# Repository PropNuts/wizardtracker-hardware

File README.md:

# STOP!

__This project has moved to GitLab:__ https://gitlab.com/PropNuts/wizardtracker-hardware

__There will be no further updates here.__

# wizardtracker-hardware

This project contains the hardware and firmware for the PropNuts WizardTracker,
an RSSI-based lap timer for drone racing.

## Hardware

The KiCad files can be found under `hardware/`.

The current revision (v2) allows for a total of either eight receivers, or six
receivers with voltage and temperature monitoring. A voltage regulator and XT60
are mounted onboard to provide power.

<p>
  
</p>

### Parts List

You can put together a full system for around ~£65.

- [RX5808s (6x or 8x)](https://www.banggood.com/FPV-5_8G-Wireless-Audio-Video-Receiving-Module-RX5808-p-84775.html?p=U103211727939201506N)
- [Arduino Nano](https://www.banggood.com/ATmega328P-Nano-V3-Controller-Board-Compatible-Arduino-p-940937.html?p=U103211727939201506N)
- [BEC (5V)](https://www.banggood.com/Diatone-Mini-2A-BEC-V2_0-Version-3_3V-5V-12V-For-RC-Multirotors-p-1032859.html?p=U103211727939201506N)
- [XT60](https://www.banggood.com/10X-XT60-Male-Female-Bullet-Connectors-Plugs-For-RC-Battery-p-958017.html?p=U103211727939201506N)
- [LM35](https://www.banggood.com/3Pcs-LM35DZ-TO-92-LM35-Precision-Centigrade-Temperature-Sensor-p-1091397.html?p=U103211727939201506N)
- [Resistors (1x 330, 1x 10k, 1x 100k)](https://www.banggood.com/Wholesale-Metal-Film-Resistor-Assorted-Kit-30-Kinds-Value-Total-600pcs-20pcs-Each-p-53320.html?p=U103211727939201506N)
- [LEDs](https://www.banggood.com/100pcs-3mm-LED-Light-emitting-Diode-5-Colors-Electronic-Component-Pack-p-1106574.html?p=U103211727939201506N)
- [Schottky Diode (1x 1N5817)](https://www.banggood.com/100-Pcs-030892-Diodes-Package-Rectifier-Schottky-8-Type-In-Component-Box-p-1164787.html?p=U103211727939201506N)
- [Pin Headers](https://www.banggood.com/10-Pcs-40-Pin-2_54mm-Single-Row-Male-Pin-Header-Strip-For-Arduino-p-918427.html?p=U103211727939201506N)

_These are affiliate links._

## Firmware

1. Grab the latest version of the Arduino IDE.
2. Clone the repository and open `firmware/firmware.ino`.
3. Edit `Config.h` to your needs.
4. Compile and flash the code.
5. Pray the magic smoke stays in.

### Protocol

On boot, the firmware opens serial at `250000bps`. After a short delay, it will
begin sending RSSI values for each module, seperated by a space, ending in a new
line. Each line is prefixd with `r `.

In calibrated output mode, values range between `0` to `255`. In raw output
mode (default), values range between `0` to  `1023`.

    < r 110 220 150 243 135 254
    < r 140 231 143 192 148 244
    ... etc

If enabled, voltage and temperature values will be sent periodically. Voltage
is prefixed with `v ` and temperature is prefixed with `t `.

    < v 16.08
    < t 56.33
    ... etc

#### Commands

The command parser is extremely niave, with little to no error checking. Expect
strange results with malformed commands. All command should end in a new line
character.

Frequencies can be set by sending `f <index> <frequency>`. These frequencies
will be saved and reloaded on startup.

    > f 0 5745
    < ok
    > f 1 5975
    < ok
    ... etc

Modules can be calibrated using `n` (minimum) and `m` (maximum). These
calibration values will be saved and reloaded on startup. The device must be
rebooted for calibration to take effect.

    [all modules set to same frequency]
    [transmitter powered down]
    > n
    < ok
    [transmitter powered up]
    > m
    < ok

Output can be toggled between raw output using `r`, and calibration output
using `s`. The default mode is raw output. This setting is saved and will be
reloaded on startup.

    > r
    < ok
    < r 395 345 299 405 514 445
    < ... etc
    > s
    < ok
    < r 0 5 8 1 10 13
    < ... etc

Information about the device can be requested using `?`. The device will respond
in the format `? <module count> <frequency 1>...<frequency n> <raw mode>`.

    > ?
    < ? 6 5695 5695 5695 5695 5695 5695 1
    [6 receivers all on 5695MHz, with raw mode enabled]
    < ok

## Acknowledgements

The source code for this project is based on [my rx5808-pro-diversity rewrite](https://github.com/Knifa/rx5808-pro-diversity/tree/tidy-up).

## License

This project is licensed under the terms of the MIT license.

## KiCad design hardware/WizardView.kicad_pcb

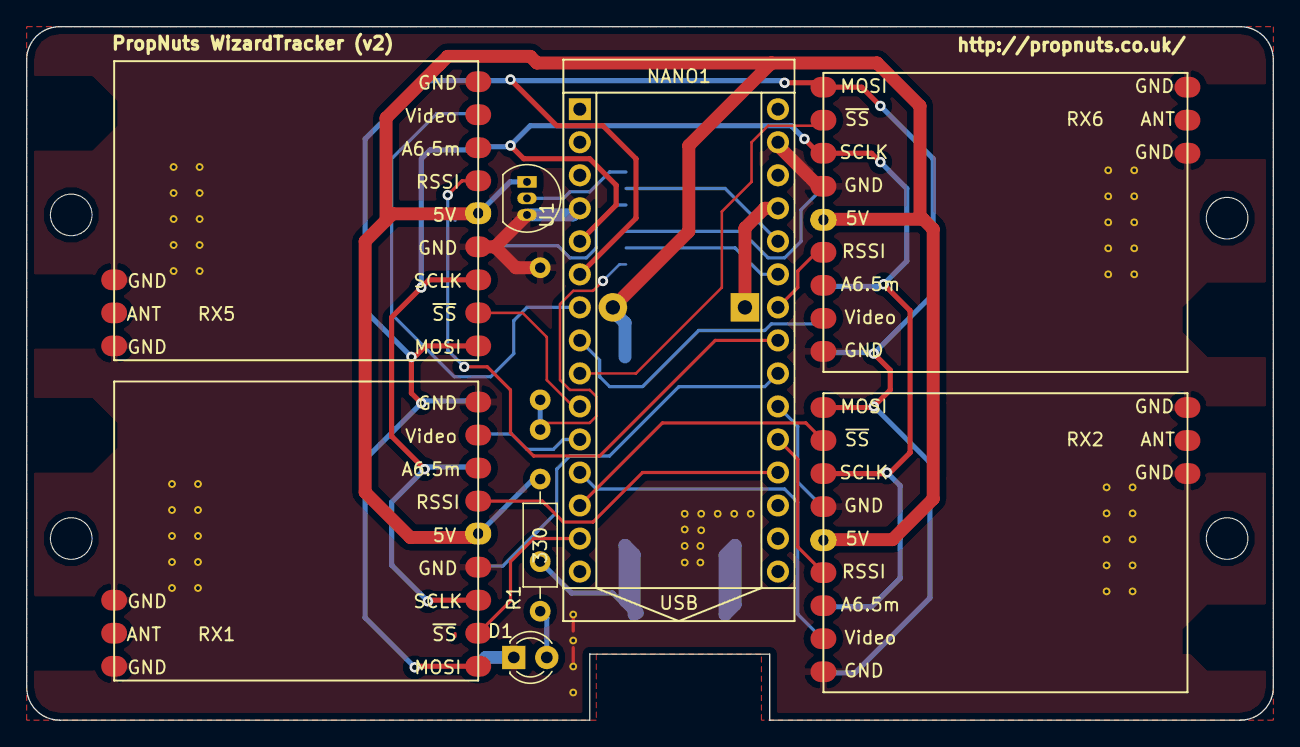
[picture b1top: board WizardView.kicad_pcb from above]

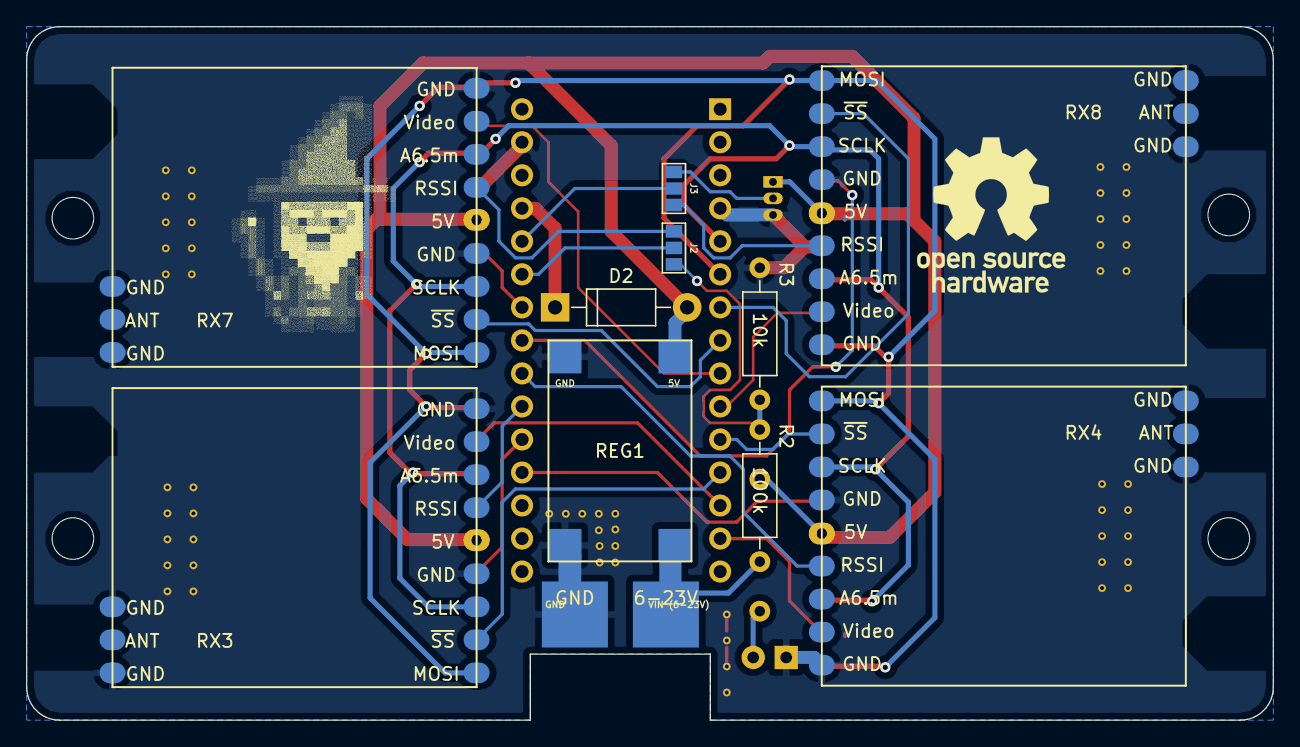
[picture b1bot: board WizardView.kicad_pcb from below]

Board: 2 copper layers, 95.9 x 53.3 mm, 19 parts (11 on the bottom side), 27 nets.

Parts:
D1: LED; LED_D3.0mm
D2: D_Schottky; D_DO-41_SOD81_P10.16mm_Horizontal
J1: CONN_01X02; XT60_5V
J2, J3: GS3
NANO1: ArduinoNano
R1: 330; R_Axial_DIN0207_L6.3mm_D2.5mm_P10.16mm_Horizontal
R2: 100k; R_Axial_DIN0207_L6.3mm_D2.5mm_P10.16mm_Horizontal
R3: 10k; R_Axial_DIN0207_L6.3mm_D2.5mm_P10.16mm_Horizontal
REG1: 5VRegulator; 5VBEC
RX1, RX2, RX3, RX4, RX5, RX6, RX7, RX8: RX5808
U1: LM35-LP; TO-92_Inline_Narrow_Oval

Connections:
+5V: D2.2, R1.1, REG1.3, RX1.5, RX2.5, RX3.5, RX4.5, RX5.5, RX6.5, RX7.5, RX8.5, U1.1
+BATT: J1.2, R2.1, REG1.1
/BATTDIV: J2.3, R2.2, R3.1
/MOSI: NANO1.6, RX1.9, RX2.9, RX3.9, RX4.9, RX5.9, RX6.9, RX7.9, RX8.9
/RSSI1: NANO1.27, RX1.4
/RSSI2: NANO1.26, RX2.4
/RSSI3: NANO1.25, RX3.4
/RSSI4: NANO1.24, RX4.4
/RSSI5: NANO1.23, RX5.4
/RSSI6: NANO1.22, RX6.4
/RSSI7: J2.1, RX7.4
/RSSI8: J3.1, RX8.4
/SCLK: NANO1.5, RX1.7, RX2.7, RX3.7, RX4.7, RX5.7, RX6.7, RX7.7, RX8.7
/TEMP: J3.3, U1.2
/~SS1: NANO1.14, RX1.8
/~SS2: NANO1.13, RX2.8
/~SS3: NANO1.12, RX3.8
/~SS4: NANO1.11, RX4.8
/~SS5: NANO1.10, RX5.8
/~SS6: NANO1.9, RX6.8
/~SS7: NANO1.8, RX7.8
/~SS8: NANO1.7, RX8.8
GND: D1.1, J1.1, NANO1.4, NANO1.17, R3.2, REG1.2, REG1.4, RX1.1, RX1.6, RX1.10, RX1.12, RX2.1, RX2.6, RX2.10, RX2.12, RX3.1, RX3.6, RX3.10, RX3.12, RX4.1, RX4.6, RX4.10, RX4.12, RX5.1, RX5.6, RX5.10, RX5.12, RX6.1, RX6.6, RX6.10, RX6.12, RX7.1, RX7.6, RX7.10, RX7.12, RX8.6, RX8.10, RX8.12, U1.3
unnamed: D1.2, R1.2
unnamed: D2.1, NANO1.19
unnamed: J2.2, NANO1.21
unnamed: J3.2, NANO1.20

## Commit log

2017-03-04 Fix function name typo for synth reg
2017-03-04 Fix broken synth reg A gen
2017-03-04 Add readme and license
2017-03-06 Drop extra line ends
2017-03-06 Attempt at fixing multiple device select
2017-03-06 Add some delays between setting channels + flash LED
2017-03-09 General tidy up, fixes, and RSSI out over serial
2017-03-31 Reduce serial delay
2017-03-31 Add stub KiCad hardware design
2017-04-06 Fix wrong frequency.
2017-09-18 Update KiCad PCB to latest revision.
2017-09-18 Update README and filenames.
2017-09-20 Shuffle filenames around to tidy up.
2017-09-20 Add PCB to README.md
2017-09-21 Implement volt/temp monitoring + configuration
2017-09-21 Add basic frequency command
2017-09-21 Add EEPROM settings
2017-09-21 Add calibration.
2017-09-25 Add command for returning device information
2017-09-25 Adjust default delay values
2017-09-25 Fix boot settle happening after trying to configure the modules.
2017-09-25 Adjust defaults again.
2017-09-25 Use prescaler ADC magic to make analog reads faster.
2017-10-11 Adjust default delay
2017-10-11 Use PROGMEM where it makes sense to do so.
2017-10-11 Round voltage/temp to 2 decimal places
2017-11-02 Explicitly specify line endings
2017-11-02 Increase loop time again
